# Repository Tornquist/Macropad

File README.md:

# Macropad

A 12-key 4x3 macropad for Cherry MX Switches designed in Eagle and
configured with QMK.

* [PCB](PCB/)
* [Bill of Materials](BOM.md)
* [Firmware](Firmware/)

## Assembled Board

## Keymap

| Base                          | Raised                        |
|:-----------------------------:|:-----------------------------:|
|    |  |

## PCB

| Top                        | Bottom                     |
|:--------------------------:|:--------------------------:|
|     |  |

## Schematic

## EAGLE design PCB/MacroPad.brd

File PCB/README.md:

# PCB

This board was designed in Eagle and relies on a collection of different
component libraries.

* [ATMEGA32U4-AU](https://www.snapeda.com/parts/ATMEGA32U4-AU/Microchip/view-part/)
* [Clueboard Libraries](https://github.com/clueboard/eagle_libs)
* [Adafruit Library](https://github.com/adafruit/Adafruit-Eagle-Library)
* supply2

## Revisions

### v20190619
* Corrected mismatched D+ and D- connections

### v20190608
* ATMEGA packaging changed from QFN to TQFP
* Crystal packaging changed from 3.2x2.5 to 3.2x5
* Replaced metric 0603 diodes with through-hole 1N4148
* Rerouted board to accommodate and balance component changes

### v20190525
* Initial Layout

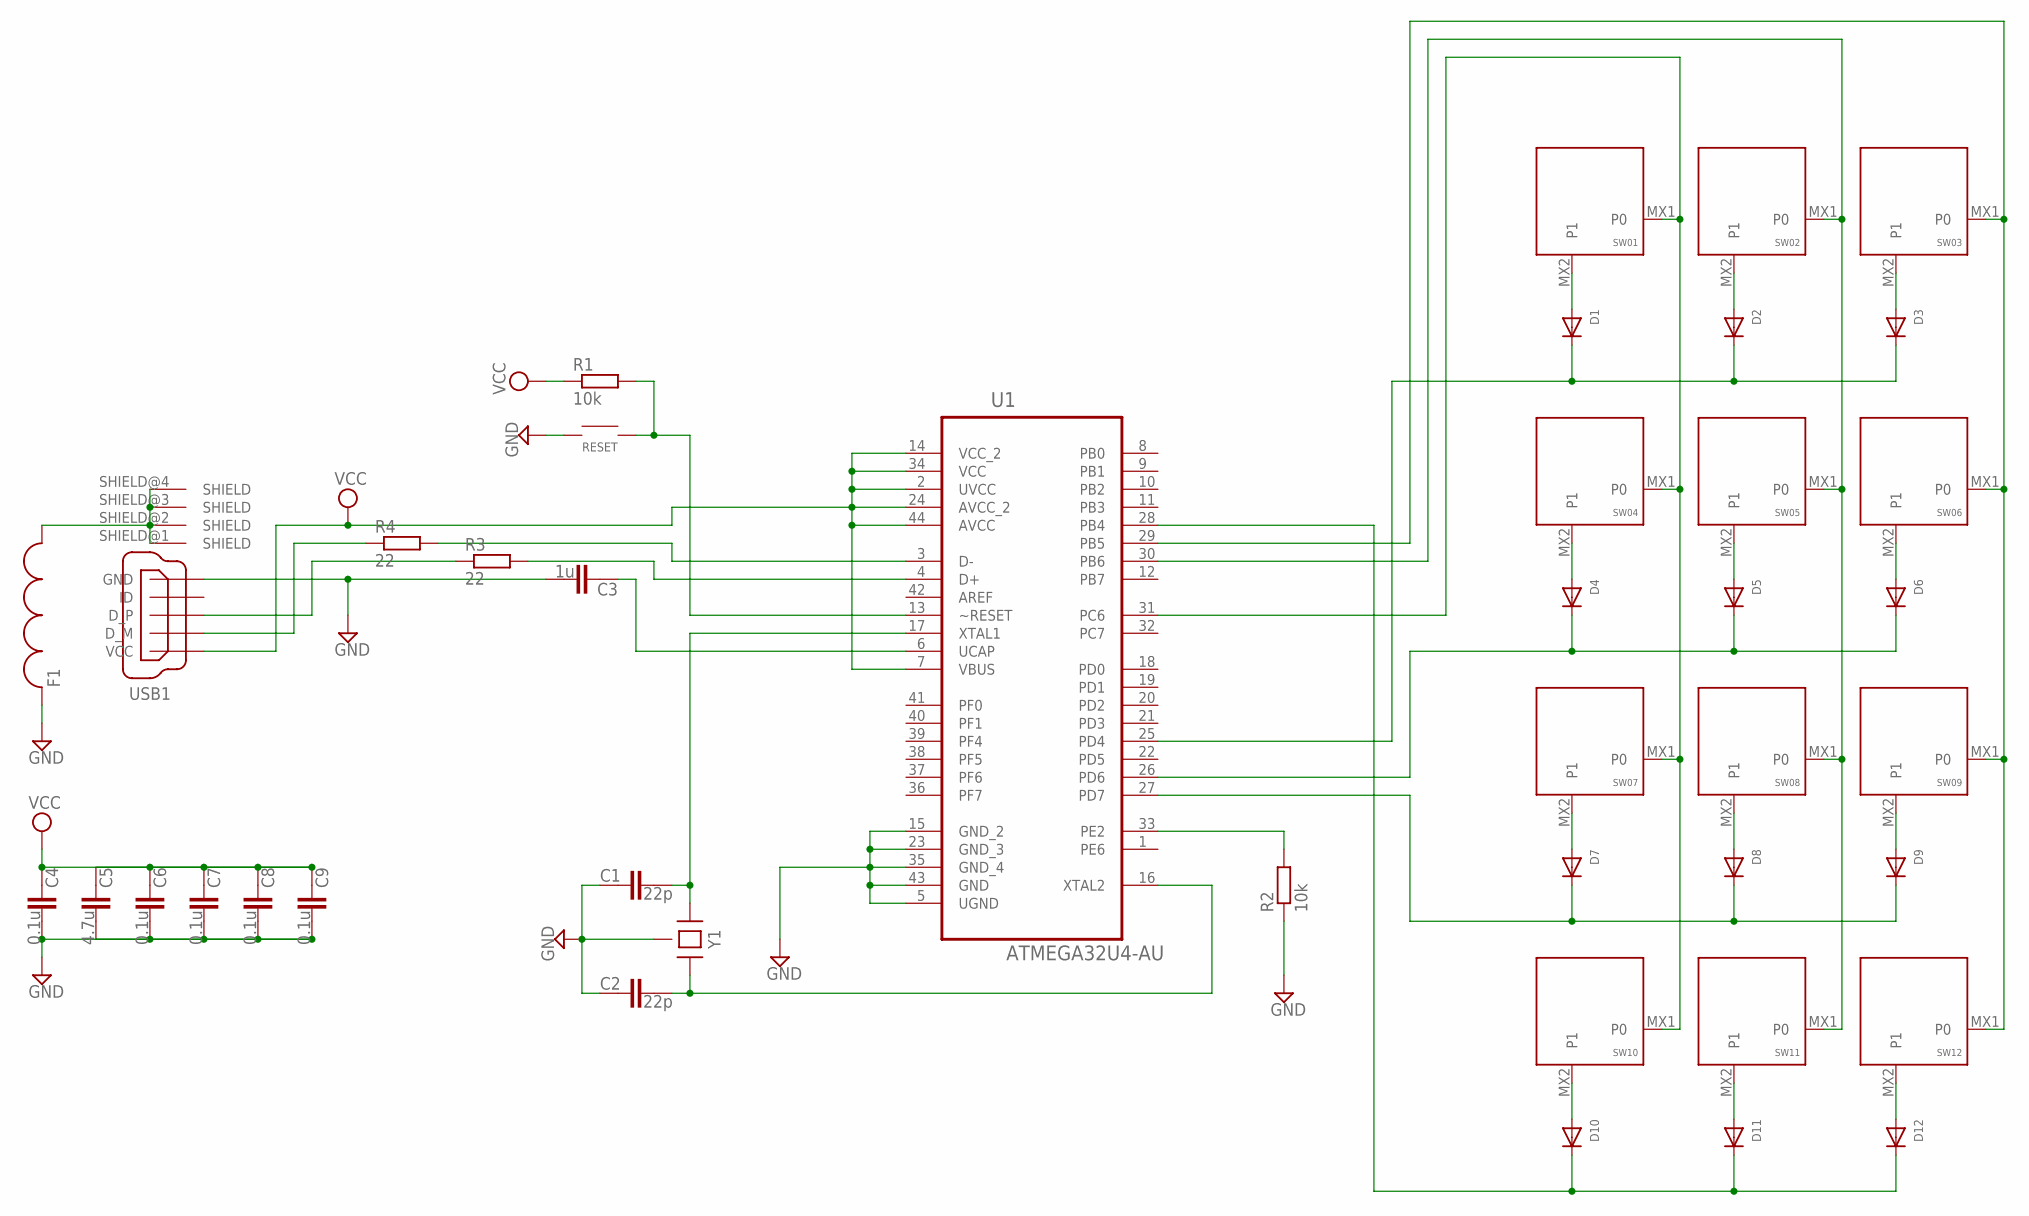
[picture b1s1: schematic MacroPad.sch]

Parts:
C1, C2: 22p; C0603; MPN 04025A220JAT2A
C3: 1u; C0603
C4, C6, C7, C8, C9: 0.1u; C0603
C5: 4.7u; C0603
D1, D2, D3, D4, D5, D6, D7, D8, D9, D10, D11, D12: DIODEDO-1N4148; DO-1N4148
F1: FERRITE-0805; F0805
R1, R2: 10k; R0603
R3, R4: 22; R0603
RESET: SWITCH-SMD-EVQP-P2602W
SW01, SW02, SW03, SW04, SW05, SW06, SW07, SW08, SW09, SW10, SW11, SW12: KEYSWITCH-PLAIN-MX-1U; MX-1U
U1: ATMEGA32U4-AU; QFP80P1200X1200X120-44N
USB1: USB_CONN-MINI-FEMALE; UX60-MB-5S8
Y1: CRYSTAL-4PIN-3.2X5; CRYSTAL-3.2X5

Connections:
GND: C1.1, C2.1, C3.2, C4.2, C5.2, C6.2, C7.2, C8.2, C9.2, F1.1, R2.1, RESET.1A (1), RESET.1B (1), U1.5 (UGND), U1.15 (GND_2), U1.23 (GND_3), U1.35 (GND_4), U1.43 (GND), USB1.GND, Y1.2 (GND), Y1.4 (GND)
unnamed: C2.2, U1.16 (XTAL2), Y1.3 (2)
unnamed: C1.2, U1.17 (XTAL1), Y1.1
unnamed: R1.2, RESET.2A (2), RESET.2B (2), U1.13 (~RESET)
unnamed: R2.2, U1.33 (PE2)
unnamed: R4.1, USB1.D- (D_M)
unnamed: R4.2, U1.3 (D-)
unnamed: R3.1, USB1.D+ (D_P)
unnamed: R3.2, U1.4 (D+)
unnamed: D1.A, SW01.MX2 (P1)
unnamed: SW01.MX1 (P0), SW04.MX1 (P0), SW07.MX1 (P0), SW10.MX1 (P0), U1.31 (PC6)
unnamed: F1.2, USB1.SHIELD@1 (SHIELD), USB1.SHIELD@2 (SHIELD), USB1.SHIELD@3 (SHIELD), USB1.SHIELD@4 (SHIELD)
unnamed: D2.A, SW02.MX2 (P1)
unnamed: D1.C, D2.C, D3.C, U1.25 (PD4)
unnamed: D3.A, SW03.MX2 (P1)
unnamed: SW03.MX1 (P0), SW06.MX1 (P0), SW09.MX1 (P0), SW12.MX1 (P0), U1.29 (PB5)
unnamed: D4.A, SW04.MX2 (P1)
unnamed: D5.A, SW05.MX2 (P1)
unnamed: D6.A, SW06.MX2 (P1)
unnamed: D4.C, D5.C, D6.C, U1.26 (PD6)
unnamed: D7.A, SW07.MX2 (P1)
unnamed: D8.A, SW08.MX2 (P1)
unnamed: D7.C, D8.C, D9.C, U1.27 (PD7)
unnamed: D9.A, SW09.MX2 (P1)
unnamed: D10.A, SW10.MX2 (P1)
unnamed: D10.C, D11.C, D12.C, U1.28 (PB4)
unnamed: D11.A, SW11.MX2 (P1)
unnamed: SW02.MX1 (P0), SW05.MX1 (P0), SW08.MX1 (P0), SW11.MX1 (P0), U1.30 (PB6)
unnamed: D12.A, SW12.MX2 (P1)
UCAP: C3.1, U1.6 (UCAP)
VCC: C4.1, C5.1, C6.1, C7.1, C8.1, C9.1, R1.1, U1.2 (UVCC), U1.7 (VBUS), U1.14 (VCC_2), U1.24 (AVCC_2), U1.34 (VCC), U1.44 (AVCC), USB1.VCC

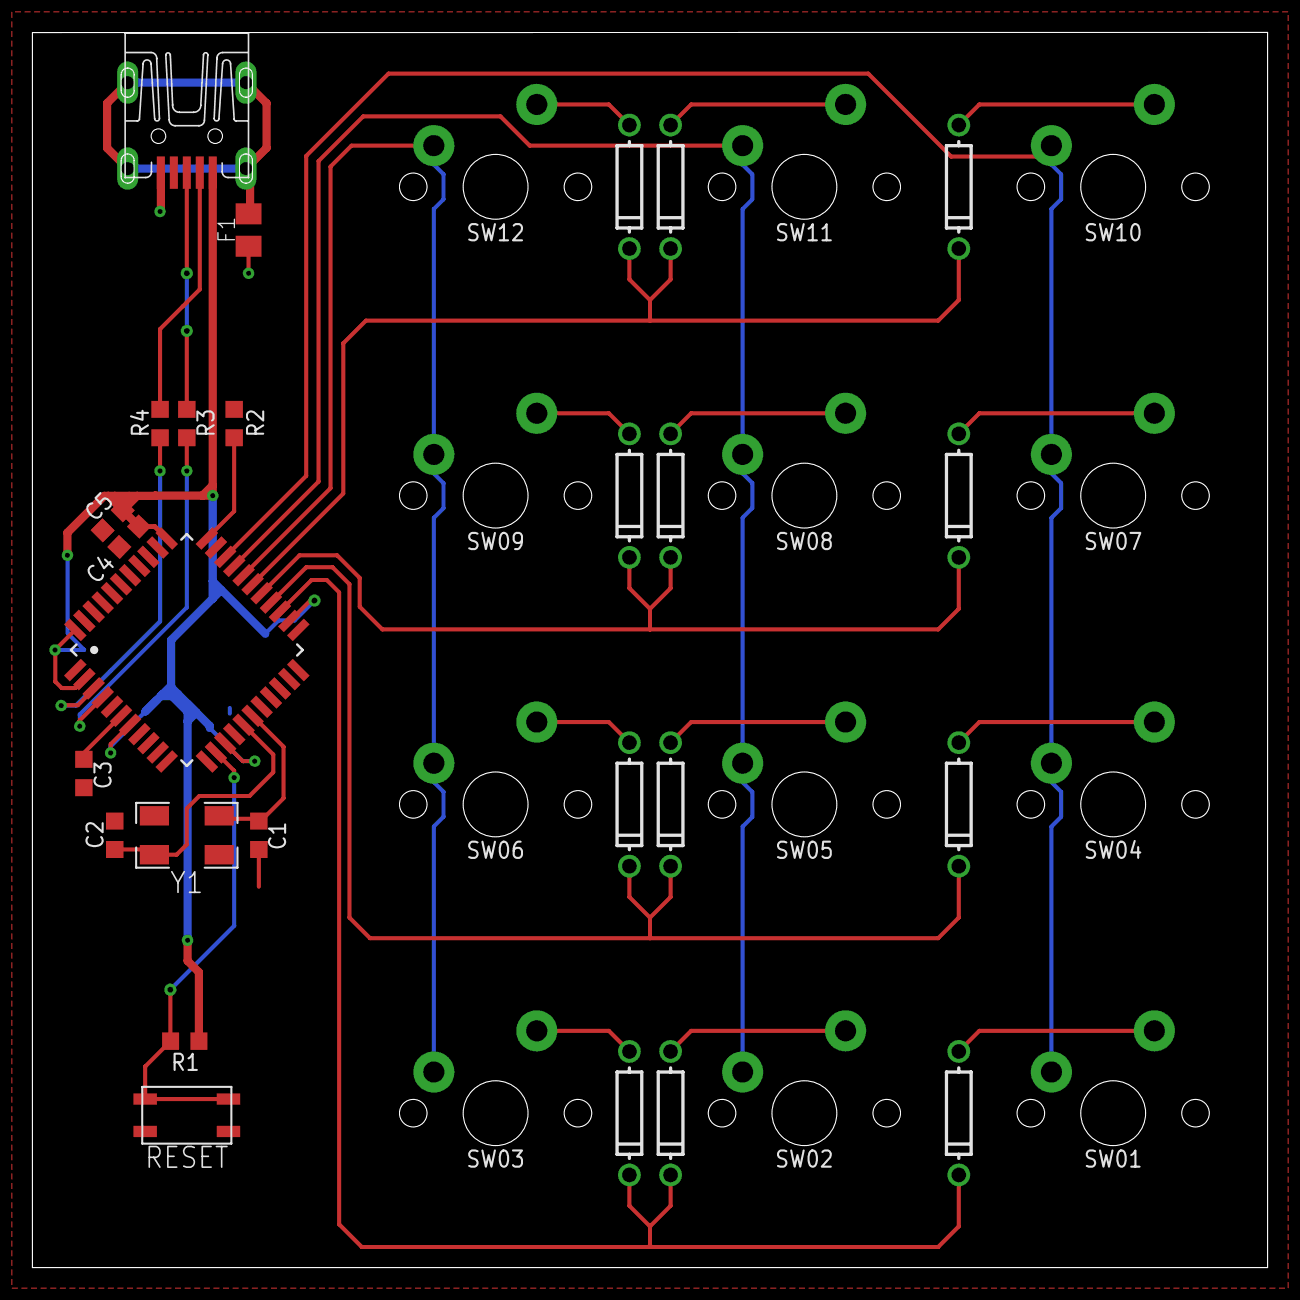
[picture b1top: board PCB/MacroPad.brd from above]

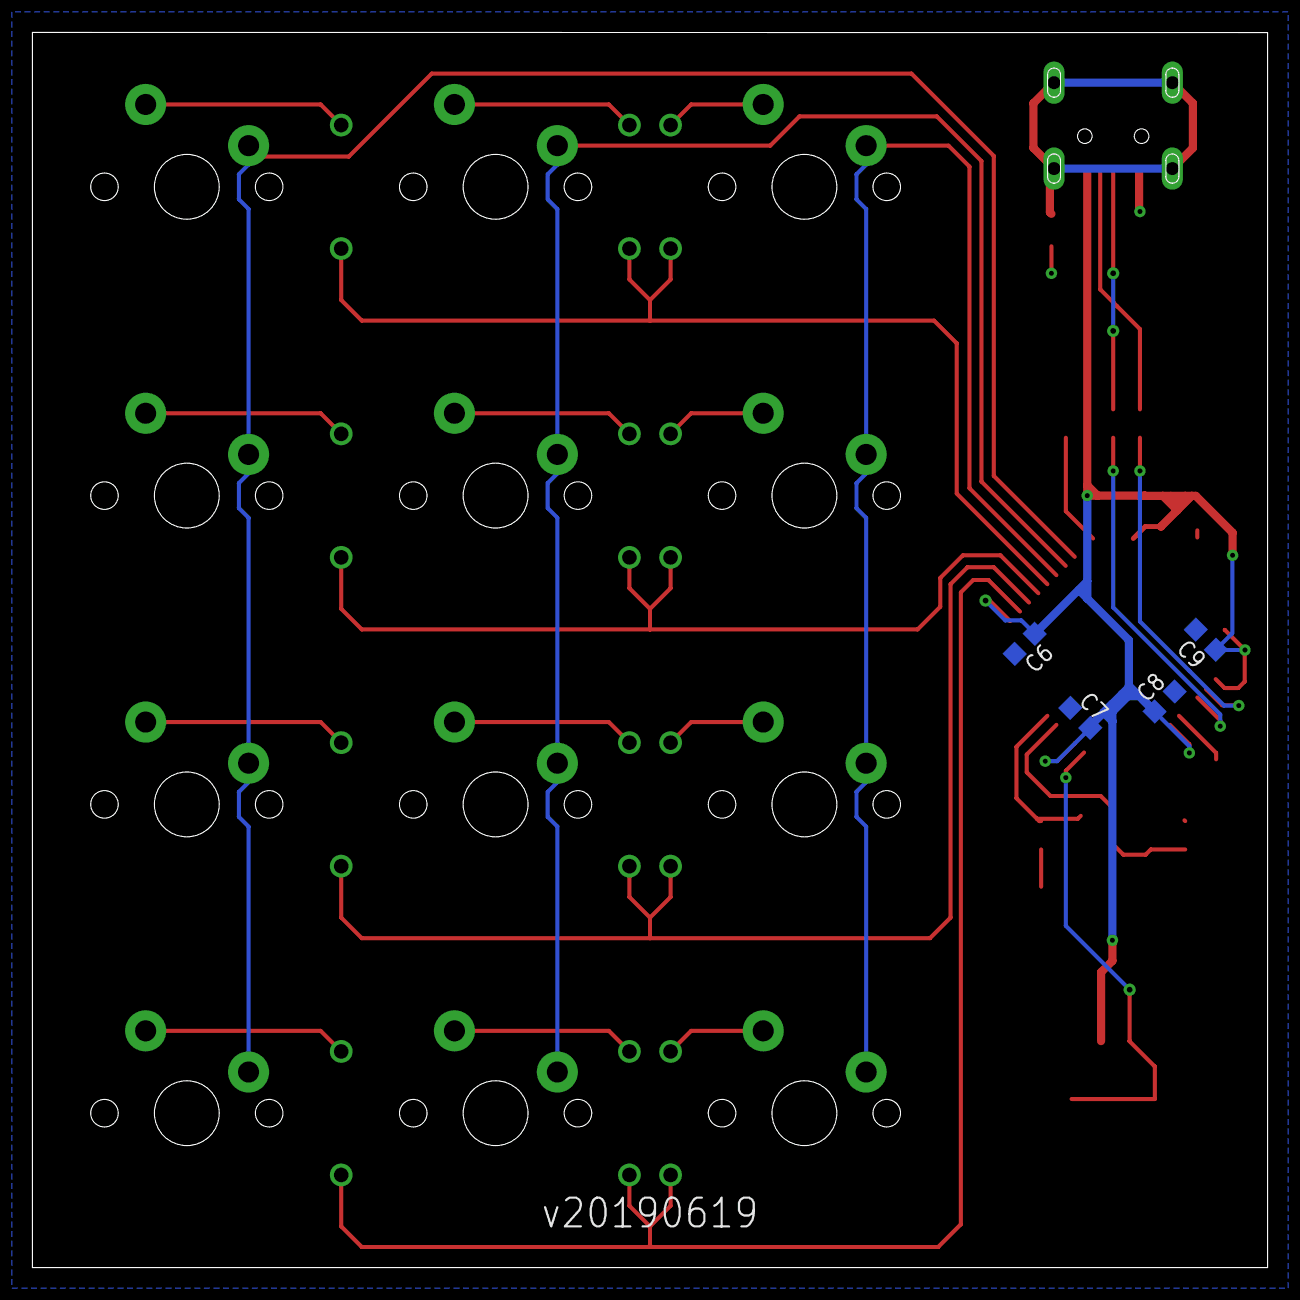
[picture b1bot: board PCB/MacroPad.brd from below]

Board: 2 copper layers, 76.2 x 76.2 mm, 42 parts (4 on the bottom side), 31 nets.

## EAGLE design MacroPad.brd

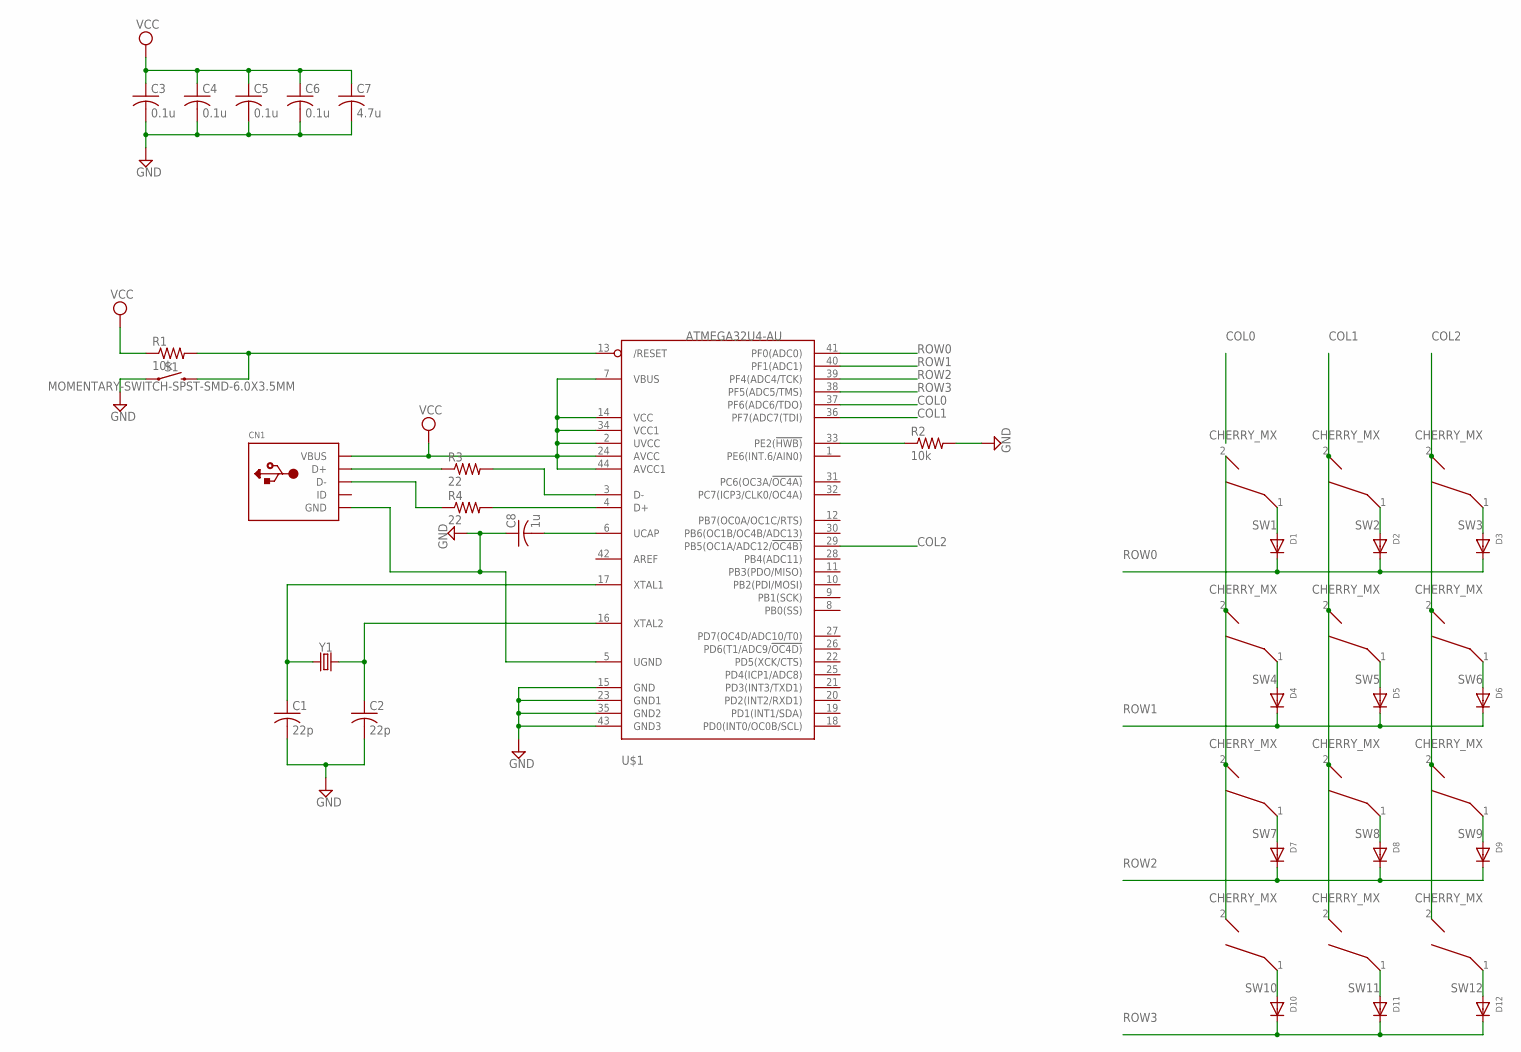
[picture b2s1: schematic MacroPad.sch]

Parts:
C1, C2: 22p; C0805
C3, C4, C5, C6: 0.1u; C0805
C7: 4.7u; C0805
C8: 1u; C0805
CN1: USBMOLEX; USB-MINIB-THM-MOLEX
D1, D2, D3, D4, D5, D6, D7, D8, D9, D10, D11, D12: DIODEDO-1N4148; DO-1N4148
R1, R2: 10k; R0805
R3, R4: 22; R0805
S1: MOMENTARY-SWITCH-SPST-SMD-6.0X3.5MM; TACTILE_SWITCH_SMD_6.0X3.5MM
SW1, SW2, SW3, SW4, SW5, SW6, SW7, SW8, SW9, SW10, SW11, SW12: CHERRY_MX; MX1A-XXNN
U$1: ATMEGA32U4-AU; TQFP44
Y1: CRYSTALSMD-5X3.2-4PAD; CRYSTAL-SMD-5X3.2-4PAD

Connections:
COL0: U$1.37 (PF6(ADC6/TDO))
COL1: SW2.2, SW5.2, SW8.2, SW11.2, U$1.36 (PF7(ADC7(TDI))
COL2: SW3.2, SW6.2, SW9.2, SW12.2, U$1.29 (PB5(OC1A/ADC12/!OC4B))
GND: C1.2, C2.2, C3.2, C4.2, C5.2, C6.2, C7.2, C8.1, CN1.GND, R2.2, S1.1, U$1.5 (UGND), U$1.15 (GND), U$1.23 (GND1), U$1.35 (GND2), U$1.43 (GND3)
unnamed: C2.1, U$1.16 (XTAL2), Y1.3 (2)
unnamed: R2.1, U$1.33 (PE2(!HWB))
unnamed: C8.2, U$1.6 (UCAP)
unnamed: C1.1, U$1.17 (XTAL1), Y1.1
unnamed: R1.2, S1.2, U$1.13 (/RESET)
unnamed: CN1.D+, R3.1
unnamed: R3.2, U$1.3 (D-)
unnamed: R4.2, U$1.4 (D+)
unnamed: CN1.D-, R4.1
unnamed: D1.A, SW1.1
unnamed: D2.A, SW2.1
unnamed: D3.A, SW3.1
unnamed: SW1.2, SW4.2, SW7.2, SW10.2
unnamed: D7.A, SW7.1
unnamed: D8.A, SW8.1
unnamed: D9.A, SW9.1
unnamed: D10.A, SW10.1
unnamed: D11.A, SW11.1
unnamed: D12.A, SW12.1
unnamed: D4.A, SW4.1
unnamed: D5.A, SW5.1
unnamed: D6.A, SW6.1
ROW0: D1.C, D2.C, D3.C, U$1.41 (PF0(ADC0))
ROW1: D4.C, D5.C, D6.C, U$1.40 (PF1(ADC1))
ROW2: D7.C, D8.C, D9.C, U$1.39 (PF4(ADC4/TCK))
ROW3: D10.C, D11.C, D12.C, U$1.38 (PF5(ADC5/TMS))
VCC: C3.1, C4.1, C5.1, C6.1, C7.1, CN1.VBUS, R1.1, U$1.2 (UVCC), U$1.7 (VBUS), U$1.14 (VCC), U$1.24 (AVCC), U$1.34 (VCC1), U$1.44 (AVCC1)

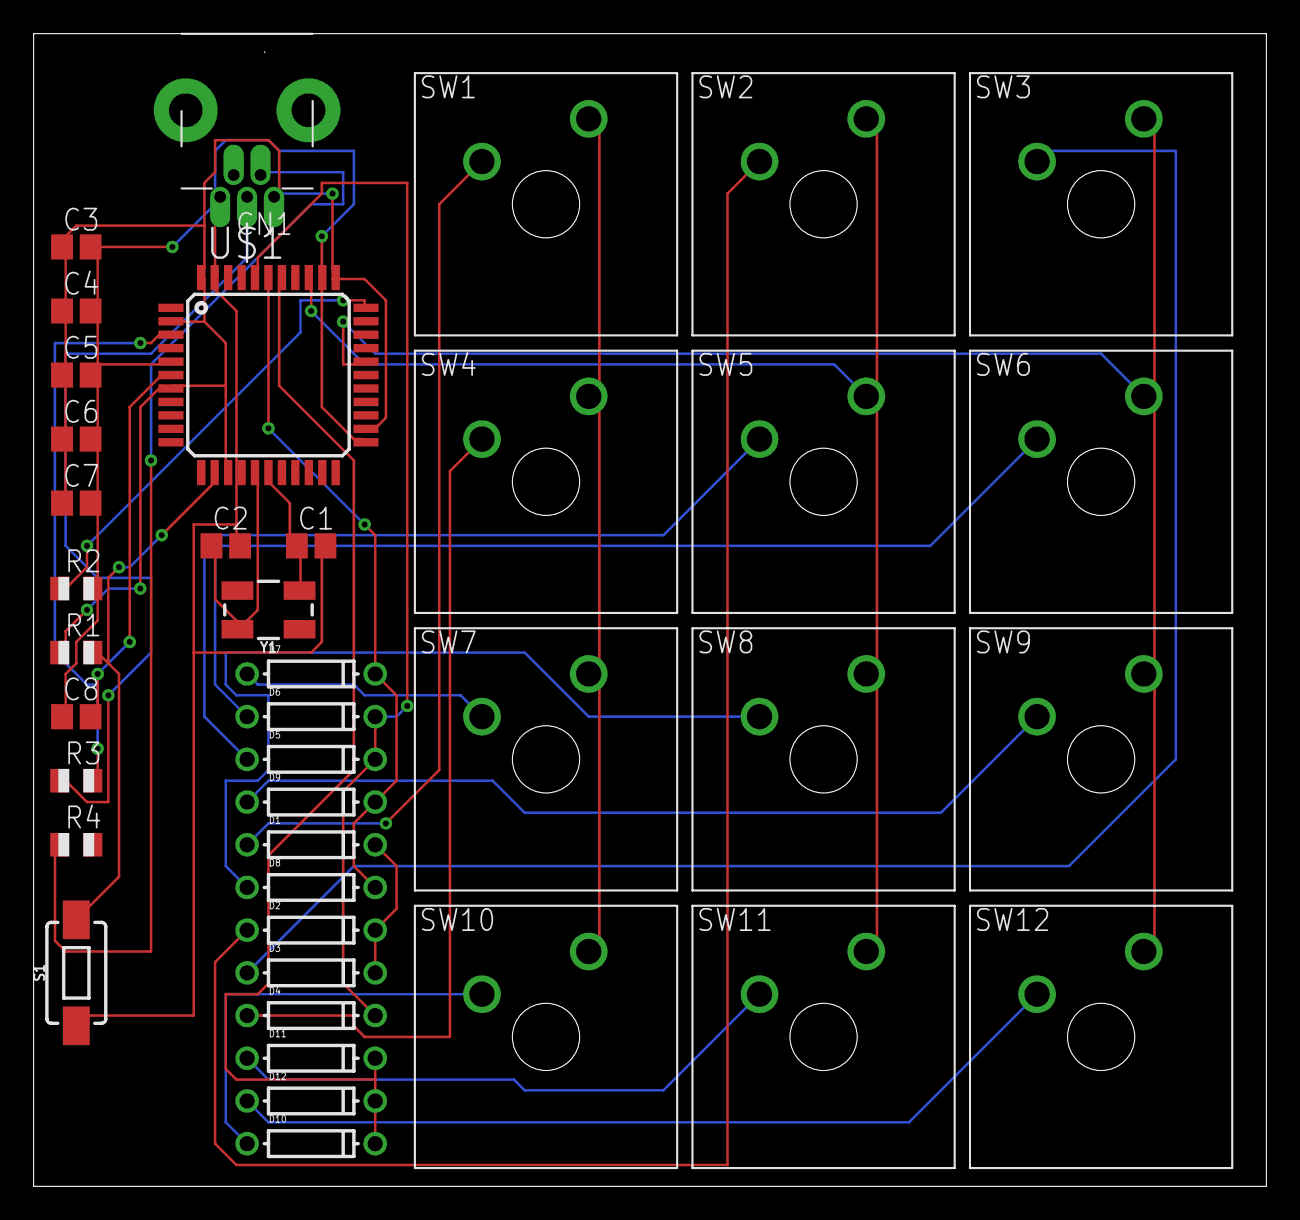
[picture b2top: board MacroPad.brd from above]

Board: 2 copper layers, 73.3 x 68.6 mm, 40 parts (0 on the bottom side), 30 nets.

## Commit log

2019-05-17 Connect processor to usb and power
2019-05-17 Add switch array and connect to microcontroller
2019-05-17 Rough board estimation: checking size
2019-05-18 Move Eagle into /Eagle and add KiCad/* schematic
2019-05-18 Keyboard schematic with associated parts
2019-05-18 Arrange components for size analysis with accurate mx switches
2019-05-21 Redo schematic in Eagle using clueboard library
2019-05-21 Create schematic and start aligning pin order
2019-05-21 Update switch and chip footprints, and switch array pins
2019-05-21 Route rows
2019-05-21 Route columns
2019-05-21 Routed board
2019-05-22 Compress row traces
2019-05-22 Components routed in compressed area
2019-05-22 Shrink board
2019-05-23 Redone schematic with smaller capacitors, fixed decoupling capacitors, and adjusted trace sizes
2019-05-23 Add top and bottom ground plane and merge gnd and ugnd
2019-05-23 Reduce acute angles and move vias farther from board
2019-05-23 Align all labels
2019-05-25 Update layout with appropriate spacing between switches (100mil border)
2019-05-25 Adjust vias position based on JLCPCB rendering
2019-05-25 Add version number to board
2019-05-25 Add Bill of Materials and README
2019-05-25 Remove working schematics and move v20190525 to PCB/
2019-06-08 Replace surface mount diodes with through hole
2019-06-08 Swap GFN for TQFP Chip -- board not updated
2019-06-08 Update board for TQFP footprint
2019-06-08 Use 5x3.2mm crystal
2019-06-08 Reroute columns to avoid vias
2019-06-08 Rename components based on board position
2019-06-08 Add label for chip orientation
2019-06-09 Add links to other components
2019-06-09 Finishing Touches: Date, cam file, row 2 routing, chip orientation indicator
2019-06-09 Use ATMEGA32U4-AU
2019-06-20 Add QMK Keyboard configuration
2019-06-20 Update PCB to correct D- and D+ mapping. Increment Date
2019-06-20 Add details on firmware flashing
2019-06-20 Added PCB Readme with eagle references
2019-06-20 Add schematic
2019-06-20 Add top and bottom pcb images
2019-06-20 Add assembled image and keymaps

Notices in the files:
parts and their libraries:
SparkFun-Switches: Licensing: Creative Commons ShareAlike 4.0 International - https://creativecommons.org/licenses/by-sa/4.0
